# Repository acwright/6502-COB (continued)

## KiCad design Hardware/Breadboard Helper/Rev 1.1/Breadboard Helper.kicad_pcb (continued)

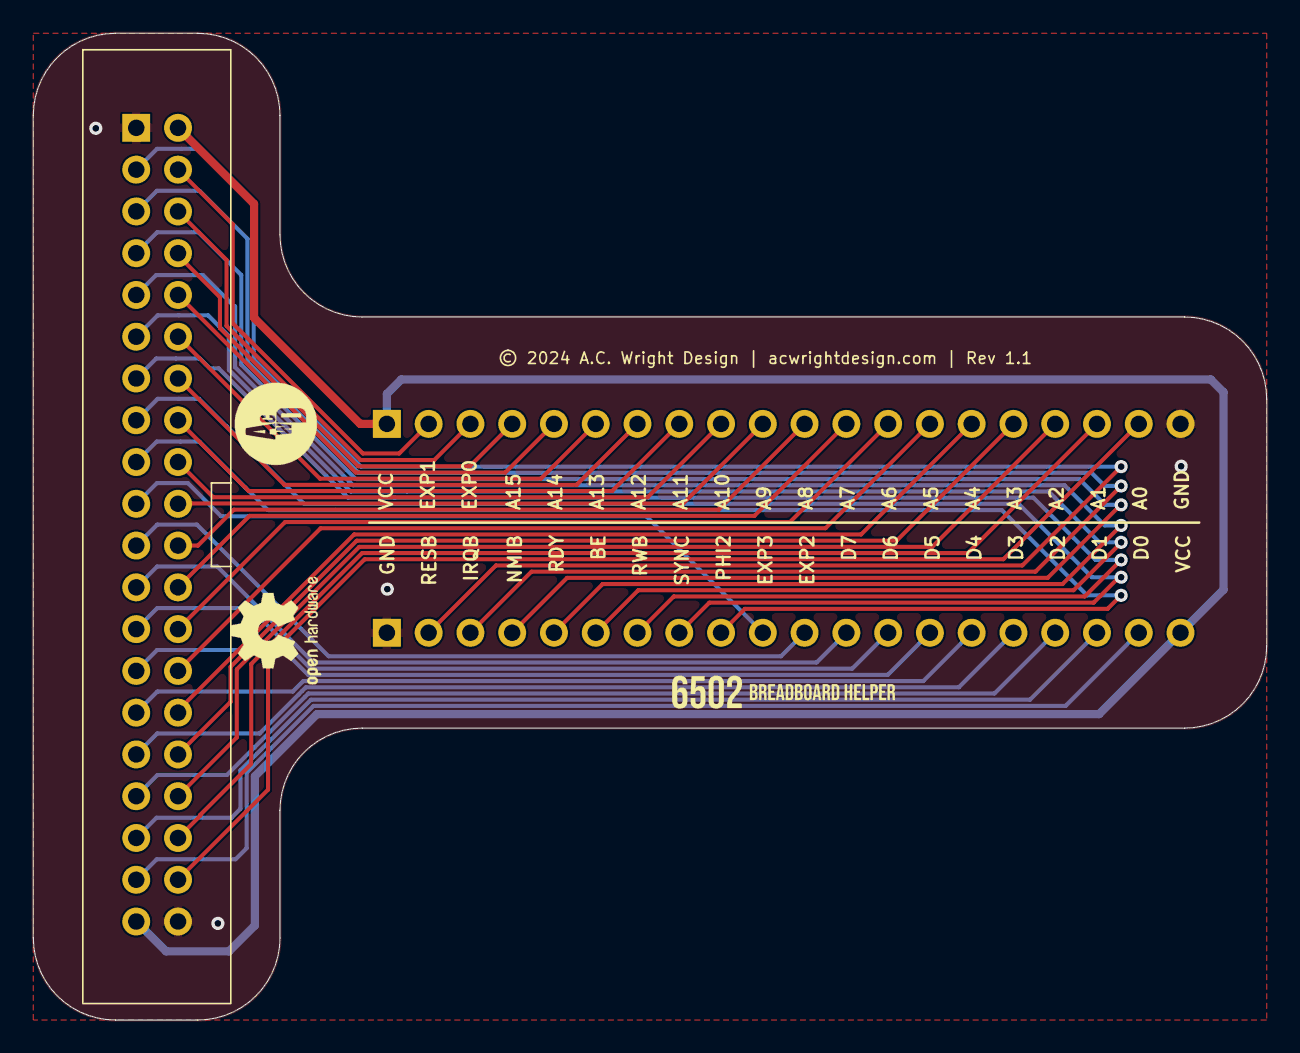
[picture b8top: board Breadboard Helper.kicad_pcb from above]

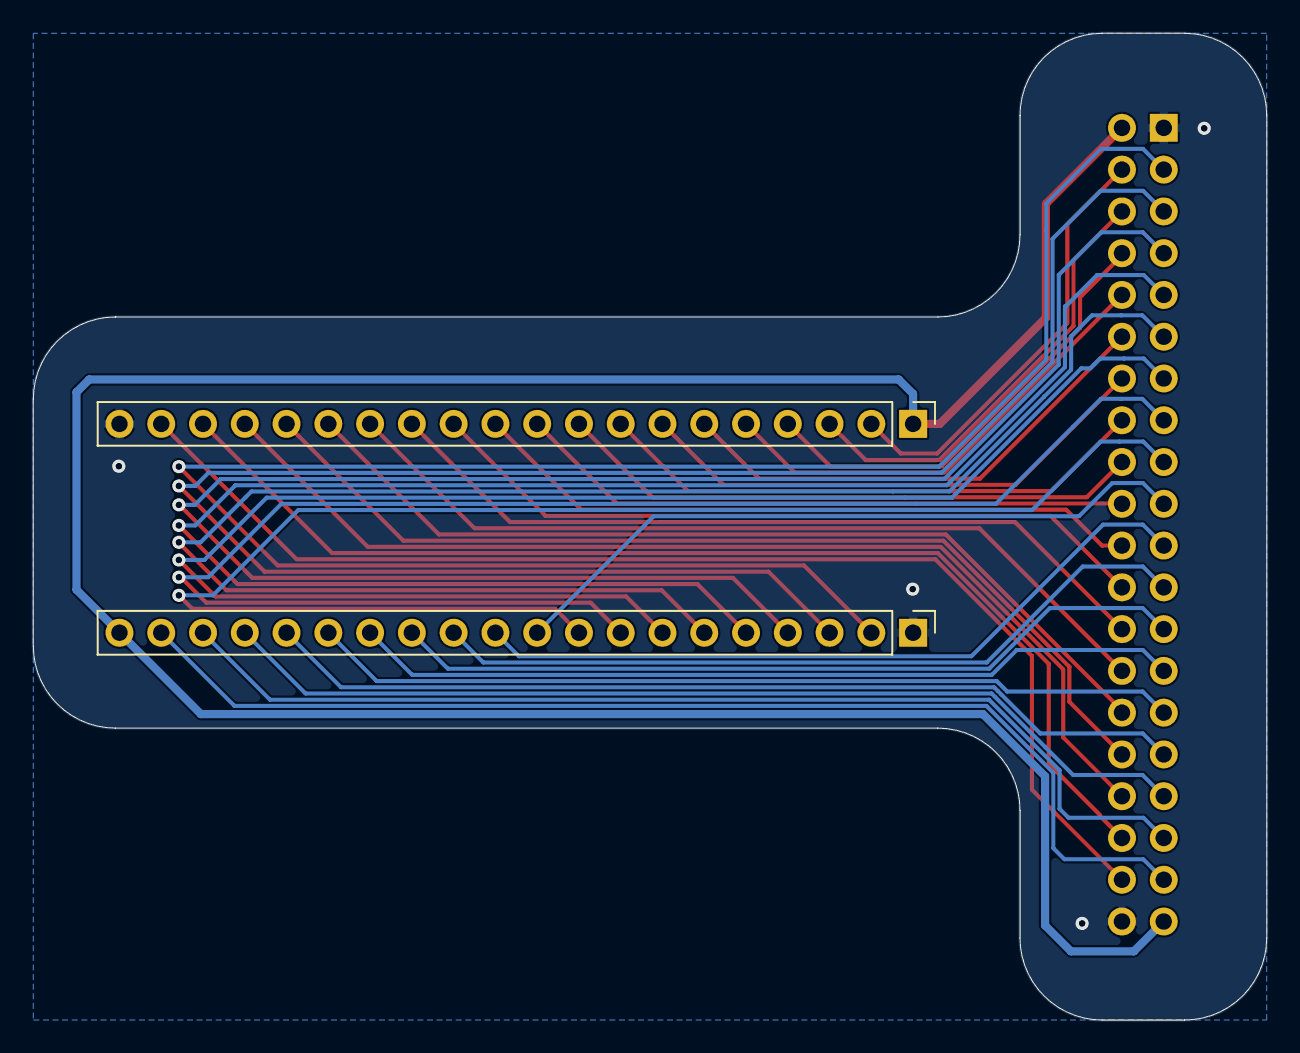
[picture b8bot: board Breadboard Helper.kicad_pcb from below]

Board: 2 copper layers, 75.0 x 60.0 mm, 3 parts (2 on the bottom side), 38 nets.

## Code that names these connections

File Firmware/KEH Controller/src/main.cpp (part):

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// ============================================================================
// Keyboard Matrix Mapping 
// ============================================================================
// Rows: PA0-PA7 (VIA Port A)
// Columns: PB0-PB7 (VIA Port B)
//
//      PB0    PB1    PB2    PB3    PB4    PB5    PB6    PB7
// PA0:  `      1      2      3      4      5      6      7
// PA1:  8      9      0      -      =      BS     ESC    TAB
// PA2:  q      w      e      r      t      y      u      i
// PA3:  o      p      [      ]      \      INS    CAPS   a
// PA4:  s      d      f      g      h      j      k      l
// PA5:  ;      '      ENTER  DEL    SHIFT  z      x      c
// PA6:  v      b      n      m      ,      .      /      UP
// PA7:  CTRL   GUI    ALT    SPACE  FN     LEFT   DOWN   RIGHT
//
// Notes:
// - BS = Backspace (0x08), ESC = Escape (0x1B), TAB (0x09)
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// Joystick State
// ============================================================================
// The two sticks share the sixteen VIA port lines with the key matrix:
// JOYSTICK A on PA0-PA7 (the matrix rows) and JOYSTICK B on PB0-PB7 (the
// columns). Every signal is active low -- the switches close to ground -- so an
// untouched stick leaves its lines pulled high.
//
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// ============================================================================
// VIA Port Access
// ============================================================================
// On the MightyCore "standard" pinout VIA_PA0-PA7 are D24-D31, which is exactly
// ATmega PORTA bits 0-7, and VIA_PB0-PB7 are D0-D7, which is exactly PORTB bits
// 0-7. Nothing else on this board lives on either register, so the whole port
// can be manipulated in a single instruction.
//
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//
// If the VIA_Px pin defines above ever change, these must change with them.

// CA2 (PD1) and CB2 (PD5) are the 6502 asking for a port back, active high.
#define CA2_RELEASE_REQUESTED() (PIND & _BV(PD1))
#define CB2_RELEASE_REQUESTED() (PIND & _BV(PD5))

// True when the 6502 has asked an encoder that is currently enabled -- and so
// currently driving a port -- to release it.
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// Maps each matrix position [row][col] to its base ASCII code (no modifiers)
// Special values: 0xFF = no key, 0xFE = modifier key (handled separately)
const uint8_t matrixMap[8][8] PROGMEM = {
  // PA0/Row 0: PB0    PB1    PB2    PB3    PB4    PB5    PB6    PB7
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  // PA1/Row 1
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  // PA2/Row 2
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  // PA3/Row 3
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  // PA4/Row 4
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  // PA5/Row 5
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  // PA6/Row 6
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  // PA7/Row 7
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};

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
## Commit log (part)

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2026-04-30 Schematic fix
2026-05-05 Project restructuring
2026-05-05 Remove Keypad Helper enclosure
2026-05-16 Add BOMs
2026-05-19 Add Keyboard Helper jig
2026-06-11 README fix
2026-06-15 Change pull up resistor values
2026-06-16 Add BOMs to README
2026-06-18 Add CPU Card Rev 1.1
2026-06-21 Silkscreen fix
2026-06-21 Add Backplane Pro Rev 1.1
